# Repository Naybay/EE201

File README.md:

# EE201
## USER INFO
 
1. **Name**
    - Nathan Holterhoff
2. **Email**
    - nholte@uw.edu
3. **NetID**
    - nholte
4. **Student Number**
    - 2062533

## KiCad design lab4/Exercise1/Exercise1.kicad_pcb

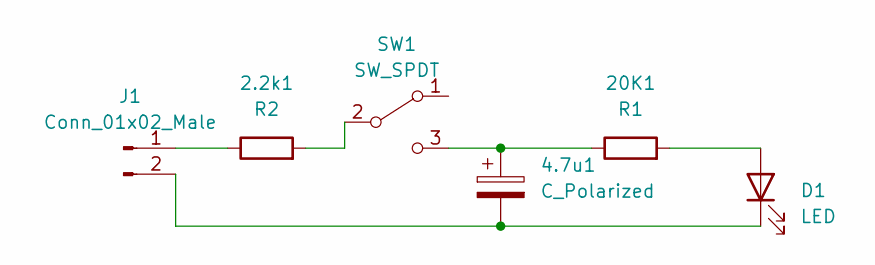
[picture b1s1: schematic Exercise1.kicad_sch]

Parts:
2.2k1: R2; R_Axial_DIN0516_L15.5mm_D5.0mm_P20.32mm_Horizontal
4.7u1: C_Polarized; C_Radial_D5.0mm_H5.0mm_P2.00mm
20K1: R1; R_Axial_DIN0516_L15.5mm_D5.0mm_P20.32mm_Horizontal
D1: LED; LED_D5.0mm
J1: Conn_01x02_Male; JST_PH_B2B-PH-K_1x02_P2.00mm_Vertical
SW1: SW_SPDT; SW_E-Switch_EG1224_SPDT_Angled

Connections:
unnamed: 2.2k1.1, J1.1
unnamed: 2.2k1.2, SW1.2 (B)
unnamed: 4.7u1.2, D1.1 (K), J1.2
unnamed: 4.7u1.1, 20K1.1, SW1.3 (C)
unnamed: 20K1.2, D1.2 (A)

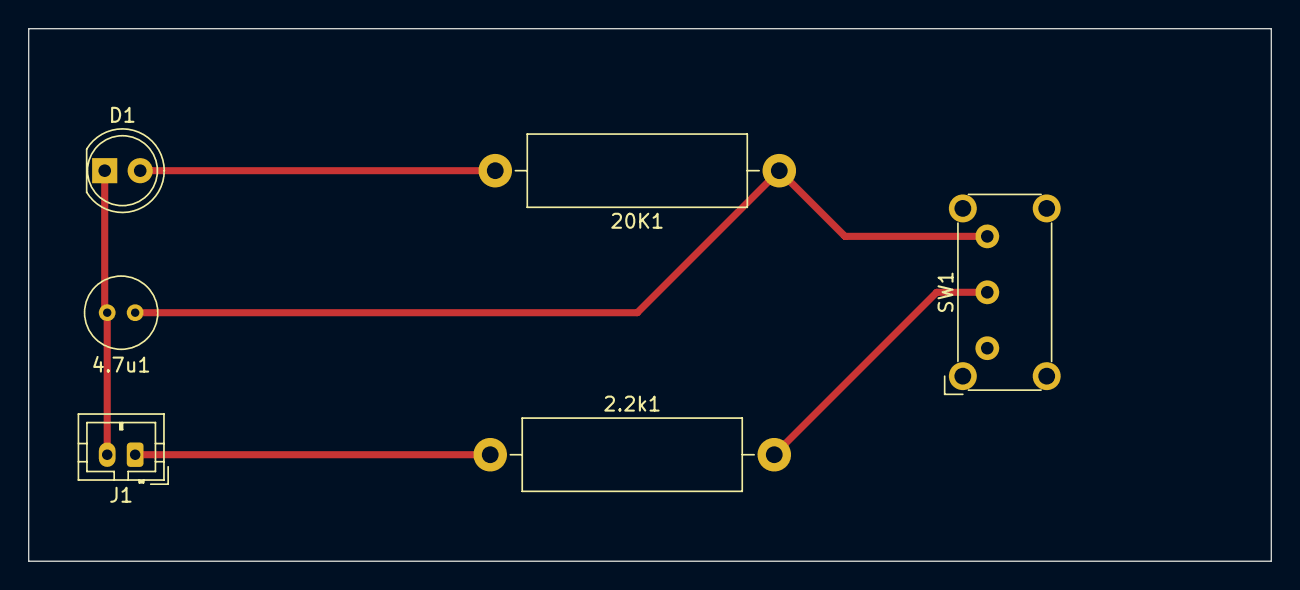
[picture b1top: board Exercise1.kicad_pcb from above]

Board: 2 copper layers, 88.9 x 38.1 mm, 6 parts (0 on the bottom side), 5 nets.

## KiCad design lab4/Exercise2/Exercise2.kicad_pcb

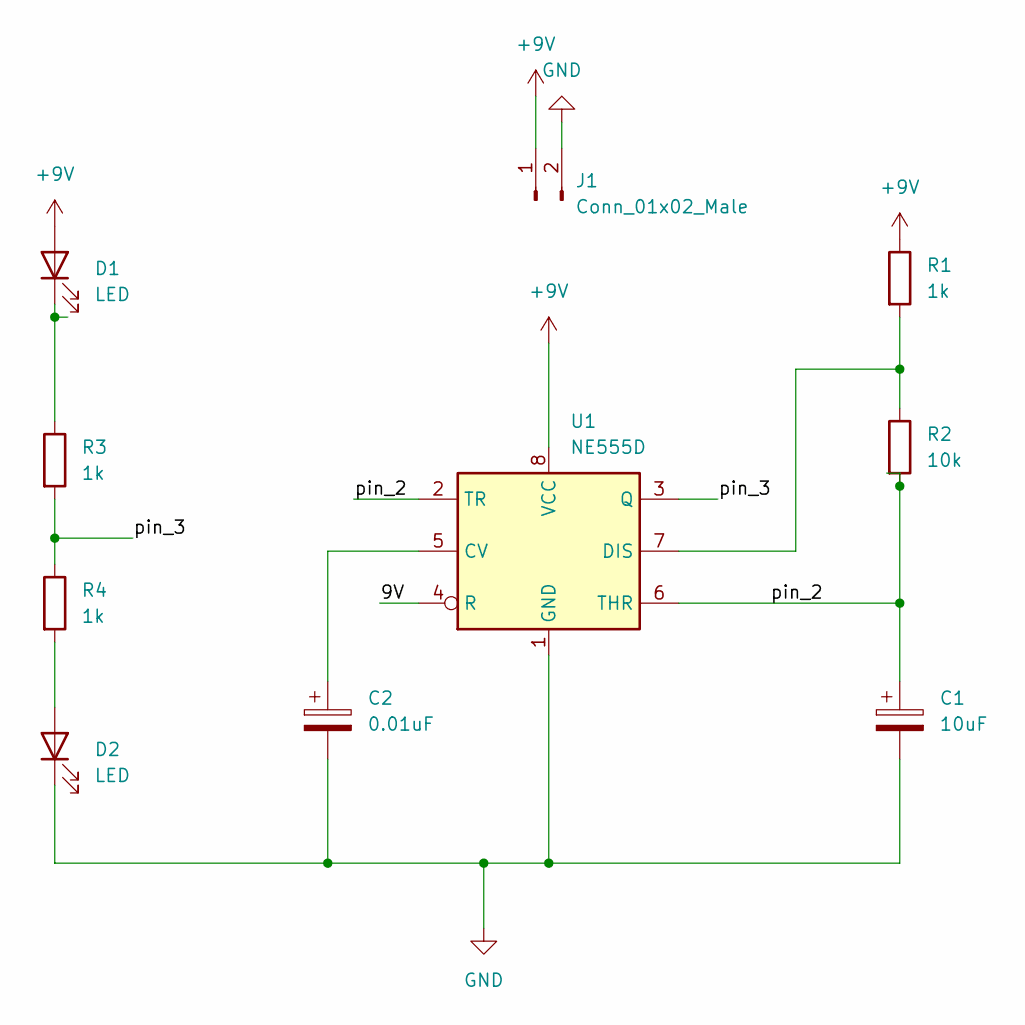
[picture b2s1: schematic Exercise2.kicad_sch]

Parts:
C1: 10uF; CP_EIA-3216-18_Kemet-A_Pad1.58x1.35mm_HandSolder
C2: 0.01uF; C_0805_2012Metric_Pad1.18x1.45mm_HandSolder
D1, D2: LED; LED_1206_3216Metric_Pad1.42x1.75mm_HandSolder
J1: Conn_01x02_Male; TerminalBlock_bornier-2_P5.08mm
R1, R3, R4: 1k; R_0805_2012Metric_Pad1.20x1.40mm_HandSolder
R2: 10k; R_0805_2012Metric_Pad1.20x1.40mm_HandSolder
U1: NE555D; SOIC-8-1EP_3.9x4.9mm_P1.27mm_EP2.29x3mm

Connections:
+9V: D1.2 (A), J1.1, R1.1, U1.8 (VCC)
/9V: U1.4 (R)
/pin_2: C1.1, R2.2, U1.2 (TR), U1.6 (THR)
/pin_3: R3.2, R4.1, U1.3 (Q)
GND: C1.2, C2.2, D2.1 (K), J1.2, U1.1 (GND)
unnamed: C2.1, U1.5 (CV)
unnamed: D1.1 (K), R3.1
unnamed: D2.2 (A), R4.2
unnamed: R1.2, R2.1, U1.7 (DIS)

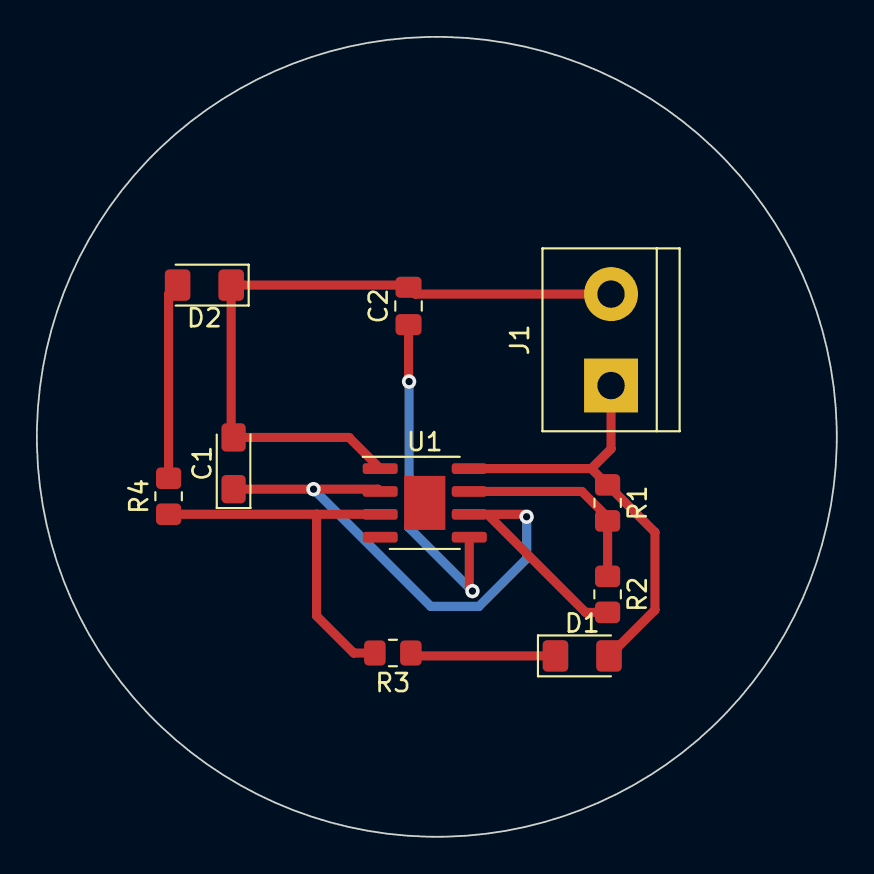
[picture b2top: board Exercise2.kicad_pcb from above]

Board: 2 copper layers, 44.4 x 44.4 mm, 10 parts (0 on the bottom side), 8 nets.

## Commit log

2023-01-12 This is all of the user info
2023-01-12 This is the base ReadMe
2023-01-12 Info about user
2023-01-19 Lab 3 code finialized
2023-01-26 Lab4 PDFs
2023-02-02 Lab5
2023-02-09 Updated to include schematics
2023-02-09 Lab6
2023-02-16 Lab 7
2023-02-16 Lab 7 updated
2023-03-11 Meter working
